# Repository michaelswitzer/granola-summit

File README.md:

# Summit by Granola Arcade

The Summit is a button box style arcade controller by Granola Arcade.

You can buy the Summit at https://granola.games

## License
The Raindrop is licensed under a <a rel="license" href="http://creativecommons.org/licenses/by-nc-sa/4.0/">Creative Commons Attribution-NonCommercial-ShareAlike 4.0 International License</a>. In simple terms, this means you are welcome to use or remix these designs to build your own controller free of cost. You are *not* permitted to sell the Summit commercially. You also can't republish the designs without attribution and without carrying this license forward into your new designs. For more information see the license file in this repository.

## How to build
To build your own Summit, import the PCB designs and bill of materials using KiCAD. I provided a list of parts that use JLCPCB's part assembly services, since that is the company I use to manufacture the PCB. You can use these files as a starting point for building your own PCB.

The .step file for the case is optimized for FDM 3D printers. I recommend PLA with at least 15% infill but you can use any material you wish. The case has designed break-away supports that you will remove after printing. It should already be aligned in the correct orientation.

The keycap files are also included, for use with Kailh Choc V2 stems (MX style). You may need to adjust the x-y hole and contour compensation values in your slicer for proper fitment.

You will need to source your own key switches. The Summit uses Kailh low-profile Choc keyboard switches.

Once you have the case, switches and keycaps, you simply slide the PCB into the top of the case and then attach the switches and keycaps to assemble. Then plug the controller into your PC and upload the firmware.

## Firmware
The Summit is designed to use the <a rel="GP2040-CE firmware" href="https://github.com/OpenStickCommunity/GP2040-CE">GP2040-CE firmware</a>.

## Credits
The Raindrop was designed by Michael Switzer. The GP2040-CE firmware is maintained by <a href="https://github.com/OpenStickCommunity">OpenStickCommunity</a>. This project was inspired by the <a href="https://github.com/jfedor2/flatbox">Flatbox</a>.

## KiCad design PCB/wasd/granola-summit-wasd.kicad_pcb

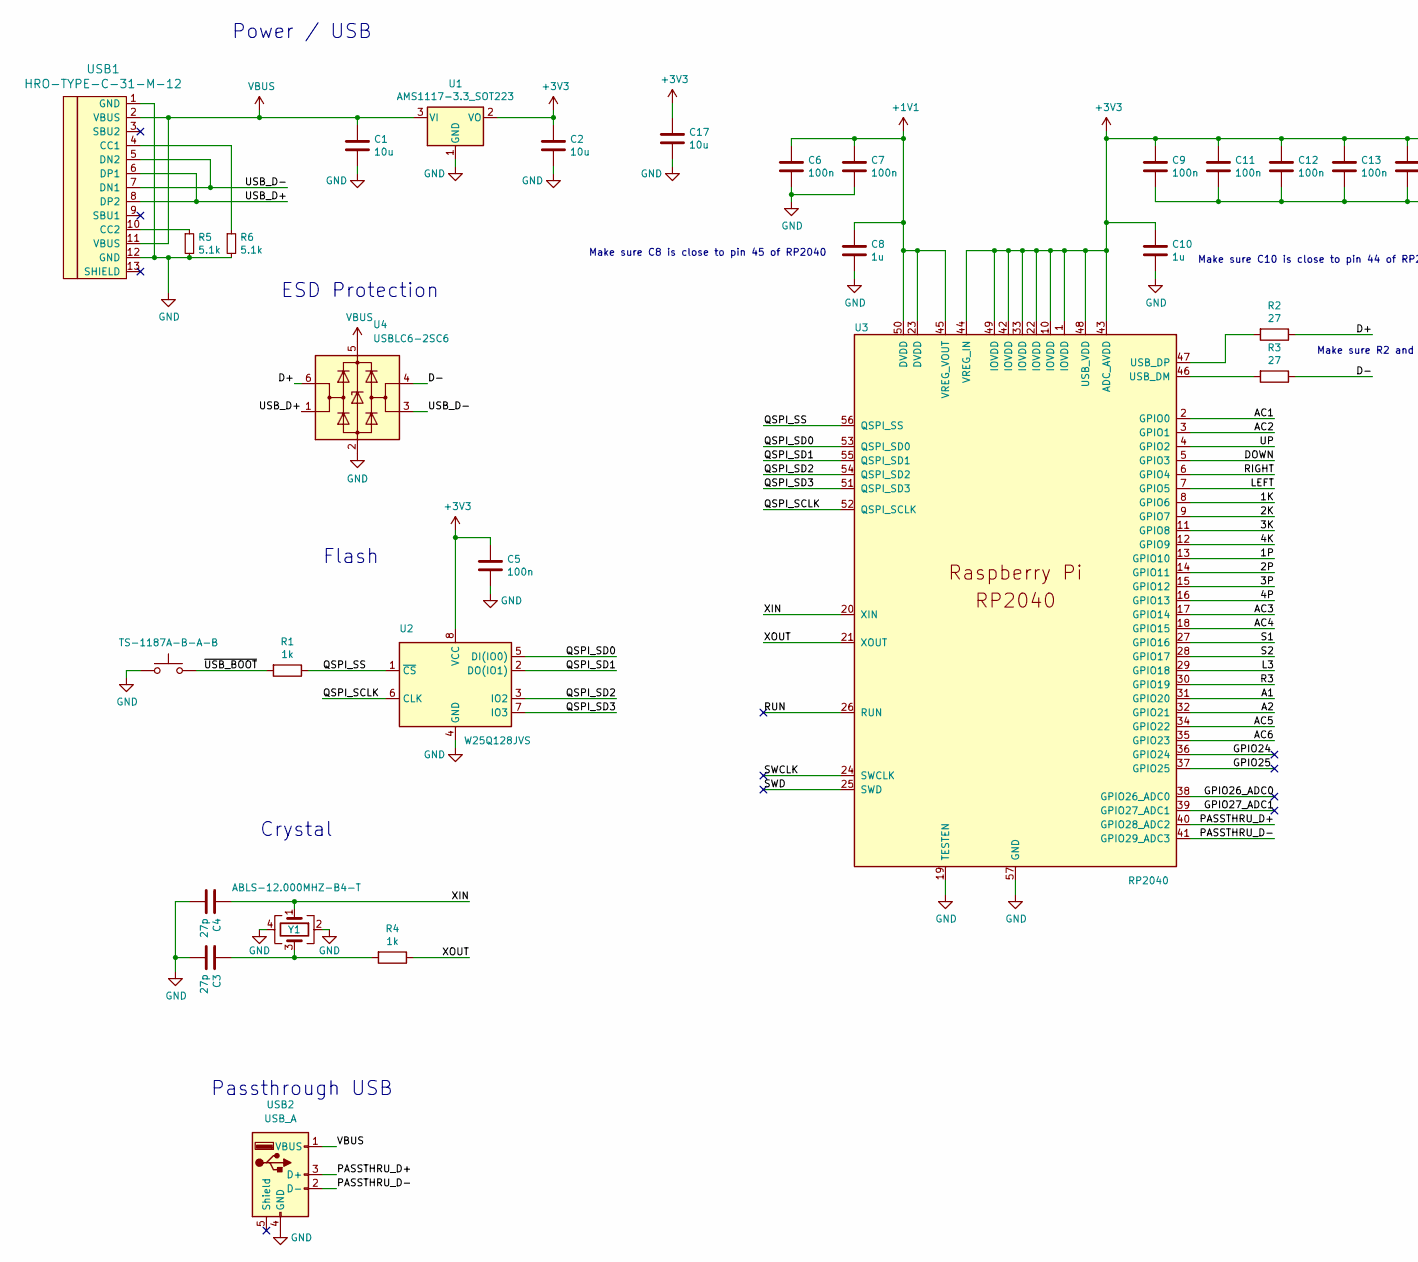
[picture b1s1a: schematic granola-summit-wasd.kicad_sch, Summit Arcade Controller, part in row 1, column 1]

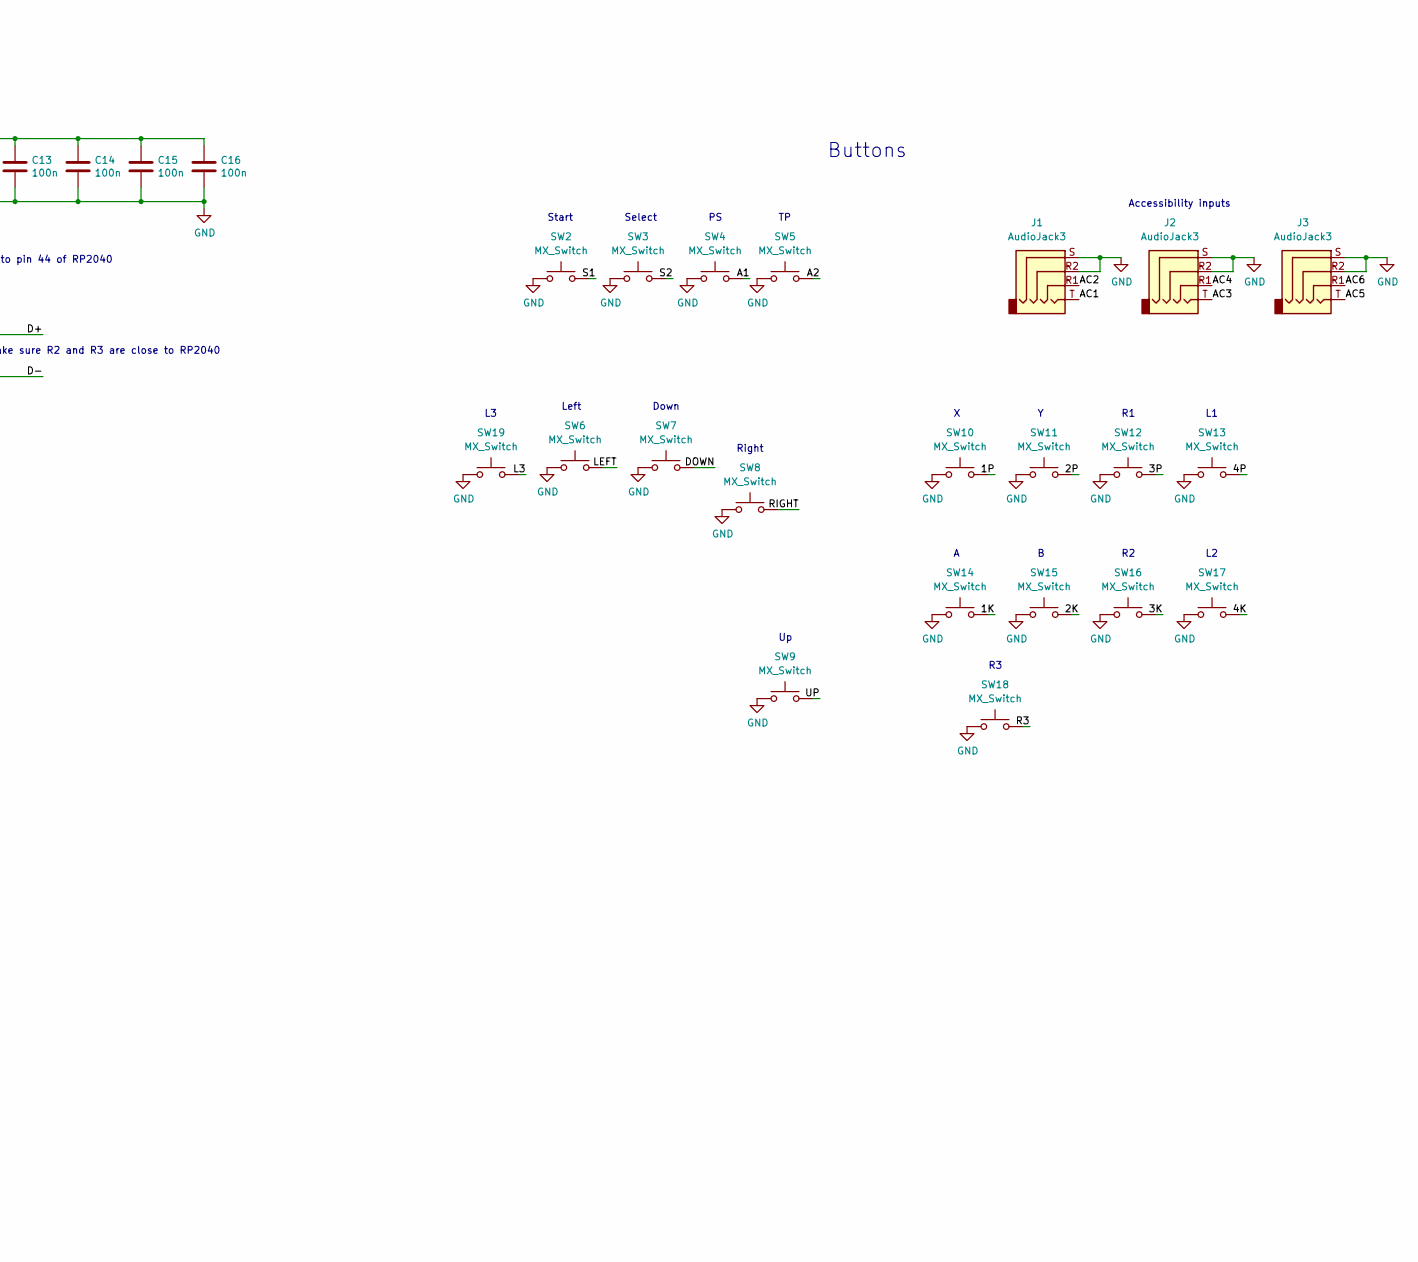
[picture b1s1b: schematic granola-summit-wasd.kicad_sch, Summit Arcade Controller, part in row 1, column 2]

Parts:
C1, C2, C17: 10u; C_0805_2012Metric; LCSC C83061
C3, C4: 27p; C_0402_1005Metric; LCSC C147436
C5, C6, C7, C9, C11, C12, C13, C14, C15, C16: 100n; C_0402_1005Metric; LCSC C115671
C8, C10: 1u; C_0402_1005Metric; LCSC C5137485
J1, J2, J3: AudioJack3; Jack_3.5mm_PJ320D_Horizontal
R1, R4: 1k; C_0402_1005Metric; LCSC C105637
R2, R3: 27; C_0402_1005Metric; LCSC C2909343
R5, R6: 5.1k; R_0402_1005Metric; LCSC C25905
SW1: TS-1187A-B-A-B; SW_Push_1P1T_XKB_TS-1187A; LCSC C318884
SW2, SW3, SW4, SW5, SW6, SW7, SW8, SW9, SW10, SW11, SW12, SW13, SW14, SW15, SW16, SW17, SW18, SW19: MX_Switch; SW_Hotswap_Kailh_Choc_V1V2_1.00u
U1: AMS1117-3.3_SOT223; SOT-223-3_TabPin2; LCSC C5250992
U2: W25Q128JVS; SOIC-8_5.23x5.23mm_P1.27mm; LCSC C97521
U3: RP2040; RP2040-QFN-56; LCSC C2040
U4: USBLC6-2SC6; SOT-23-6
USB1: HRO-TYPE-C-31-M-12; HRO-TYPE-C-31-M-12-Assembly; LCSC C165948
USB2: USB_A; USB-A-SMD_C42591; LCSC C42591
Y1: ABLS-12.000MHZ-B4-T; Crystal_SMD_3225-4Pin_3.2x2.5mm; LCSC C9002

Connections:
+1V1: C6.1, C7.1, C8.1, U3.23 (DVDD), U3.45 (VREG_VOUT), U3.50 (DVDD)
+3V3: C2.1, C5.1, C9.1, C10.1, C11.1, C12.1, C13.1, C14.1, C15.1, C16.1, C17.1, U1.2 (VO), U2.8 (VCC), U3.1 (IOVDD), U3.10 (IOVDD), U3.22 (IOVDD), U3.33 (IOVDD), U3.42 (IOVDD), U3.43 (ADC_AVDD), U3.44 (VREG_IN), U3.48 (USB_VDD), U3.49 (IOVDD)
/1K: SW14.1 (A), U3.8 (GPIO6)
/1P: SW10.1 (A), U3.13 (GPIO10)
/2K: SW15.1 (A), U3.9 (GPIO7)
/2P: SW11.1 (A), U3.14 (GPIO11)
/3K: SW16.1 (A), U3.11 (GPIO8)
/3P: SW12.1 (A), U3.15 (GPIO12)
/4K: SW17.1 (A), U3.12 (GPIO9)
/4P: SW13.1 (A), U3.16 (GPIO13)
/A1: SW4.1 (A), U3.31 (GPIO20)
/A2: SW5.1 (A), U3.32 (GPIO21)
/AC1: J1.T, U3.2 (GPIO0)
/AC2: J1.R1, U3.3 (GPIO1)
/AC3: J2.T, U3.17 (GPIO14)
/AC4: J2.R1, U3.18 (GPIO15)
/AC5: J3.T, U3.34 (GPIO22)
/AC6: J3.R1, U3.35 (GPIO23)
/D+: R2.1, U4.6 (I/O1)
/D-: R3.1, U4.4 (I/O2)
/DOWN: SW7.1 (A), U3.5 (GPIO3)
/GPIO24: U3.36 (GPIO24)
/GPIO25: U3.37 (GPIO25)
/GPIO26_ADC0: U3.38 (GPIO26_ADC0)
/GPIO27_ADC1: U3.39 (GPIO27_ADC1)
/L3: SW19.1 (A), U3.29 (GPIO18)
/LEFT: SW6.1 (A), U3.7 (GPIO5)
/PASSTHRU_D+: U3.40 (GPIO28_ADC2), USB2.3 (D+)
/PASSTHRU_D-: U3.41 (GPIO29_ADC3), USB2.2 (D-)
/QSPI_SCLK: U2.6 (CLK), U3.52 (QSPI_SCLK)
/QSPI_SD0: U2.5 (DI(IO0)), U3.53 (QSPI_SD0)
/QSPI_SD1: U2.2 (DO(IO1)), U3.55 (QSPI_SD1)
/QSPI_SD2: U2.3 (IO2), U3.54 (QSPI_SD2)
/QSPI_SD3: U2.7 (IO3), U3.51 (QSPI_SD3)
/QSPI_SS: R1.1, U2.1 (~CS), U3.56 (QSPI_SS)
/R3: SW18.1 (A), U3.30 (GPIO19)
/RIGHT: SW8.1 (A), U3.6 (GPIO4)
/RUN: U3.26 (RUN)
/S1: SW2.1 (A), U3.27 (GPIO16)
/S2: SW3.1 (A), U3.28 (GPIO17)
/SWCLK: U3.24 (SWCLK)
/SWD: U3.25 (SWD)
/UP: SW9.1 (A), U3.4 (GPIO2)
/USB_D+: U4.1 (I/O1), USB1.6 (DP1), USB1.8 (DP2)
/USB_D-: U4.3 (I/O2), USB1.5 (DN2), USB1.7 (DN1)
/XIN: C4.1, U3.20 (XIN), Y1.1
/XOUT: R4.1, U3.21 (XOUT)
/~USB_BOOT: R1.2, SW1.1
GND: C1.2, C2.2, C3.2, C4.2, C5.2, C6.2, C7.2, C8.2, C9.2, C10.2, C11.2, C12.2, C13.2, C14.2, C15.2, C16.2, C17.2, J1.R2, J1.S, J2.R2, J2.S, J3.R2, J3.S, R5.2, R6.2, SW1.2, SW2.2 (B), SW3.2 (B), SW4.2 (B), SW5.2 (B), SW6.2 (B), SW7.2 (B), SW8.2 (B), SW9.2 (B), SW10.2 (B), SW11.2 (B), SW12.2 (B), SW13.2 (B), SW14.2 (B), SW15.2 (B), SW16.2 (B), SW17.2 (B), SW18.2 (B), SW19.2 (B), U1.1 (GND), U2.4 (GND), U3.19 (TESTEN), U3.57 (GND), U4.2 (GND), USB1.1 (GND), USB1.12 (GND), USB2.4 (GND), Y1.2, Y1.4
unnamed: C3.1, R4.2, Y1.3
unnamed: R3.2, U3.46 (USB_DM)
unnamed: R2.2, U3.47 (USB_DP)
unnamed: R6.1, USB1.4 (CC1)
unnamed: R5.1, USB1.10 (CC2)
VBUS: C1.1, U1.3 (VI), U4.5 (VBUS), USB1.2 (VBUS), USB1.11 (VBUS), USB2.1 (VBUS)

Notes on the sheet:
ESD Protection
Right
Start
Down
Left
Make sure R2 and R3 are close to RP2040
Crystal
Passthrough USB
Make sure C10 is close to pin 44 of RP2040
Flash
Accessibility inputs
Power / USB
Select
Buttons
Make sure C8 is close to pin 45 of RP2040

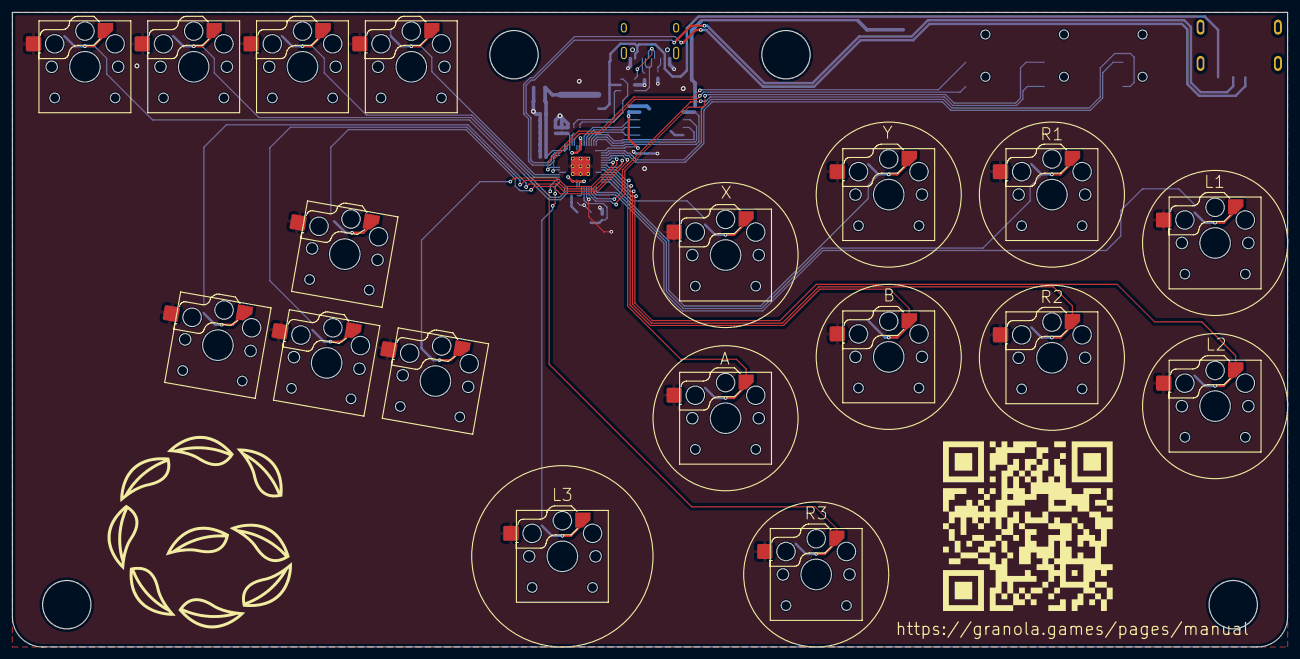
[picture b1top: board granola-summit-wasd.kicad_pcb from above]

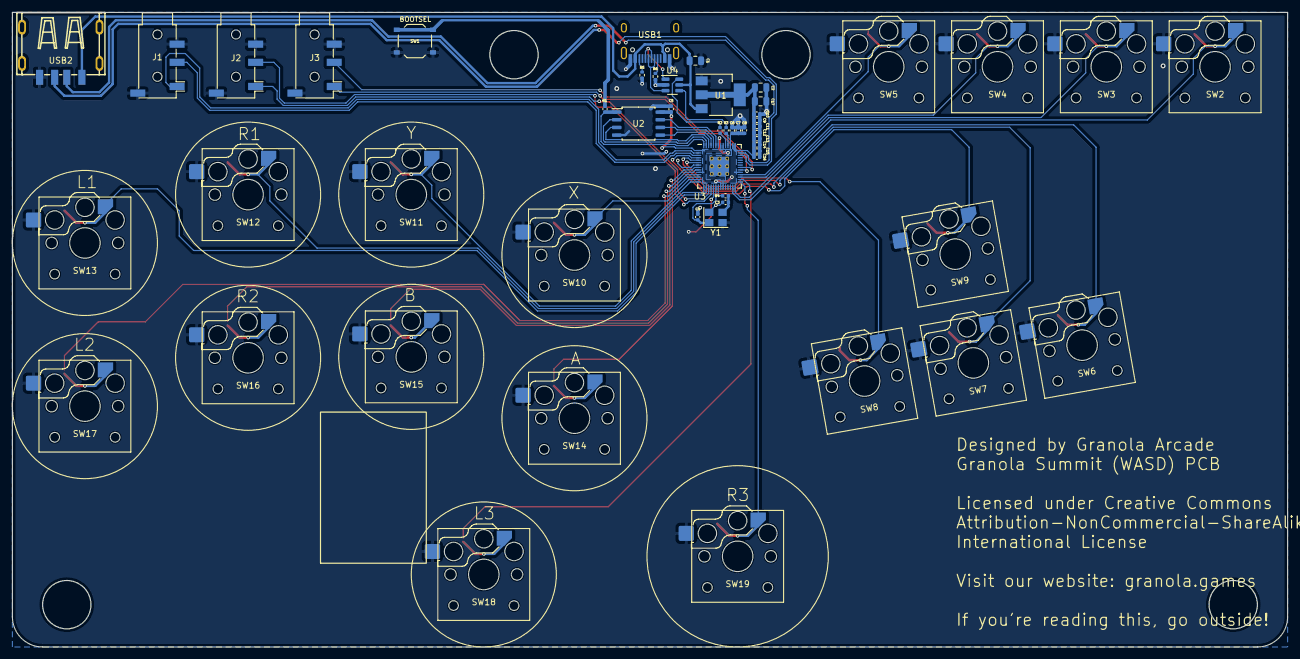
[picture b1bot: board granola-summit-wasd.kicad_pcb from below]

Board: 2 copper layers, 210.9 x 104.9 mm, 52 parts (52 on the bottom side), 48 nets.

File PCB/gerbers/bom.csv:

Comment,Designator,Footprint,LCSC Part Number
10uF,"C1,C2",Capacitor_SMD:C_0805_2012Metric,C83061
27p,"C3,C4",Capacitor_SMD:C_0402_1005Metric,C147436
100nF,"C5,C6,C7,C9,C11,C12,C13,C14,C15,C16",Capacitor_SMD:C_0402_1005Metric,C115671
1uF,"C8,C10",Capacitor_SMD:C_0402_1005Metric,C5137485
10uF,C17,Capacitor_SMD:C_0805_2012Metric,C83061
"HRO-TYPE-C-31-M-12","USB1","Type-C:HRO-TYPE-C-31-M-12-Assembly","C165948"
"USB_A","USB2","USB-A-SMD_C42591","C42591"
1k,"R1,R5",Capacitor_SMD:C_0402_1005Metric,C105637
"5.1k","R6,R7","Resistor_SMD:R_0402_1005Metric","C25905"
27 ohm,"R3,R4,R8,R9",Capacitor_SMD:C_0402_1005Metric,C2909343
MX_Switch,"SW1,SW2,SW3,SW4,SW5,SW6,SW7,SW8,SW9,SW10,SW11,SW12,SW13,SW14,SW15,SW16,SW17,SW18","Kailh:SW_Hotswap_Kailh_Choc_V1V2_1.00u_reversible,Kailh:SW_Hotswap_Kailh_Choc_V1V2_1.00u_24mm_reversible,Kailh:SW_Hotswap_Kailh_Choc_V1V2_1.00u_30mm_reversible",C5333465
AMS1117,U1,Package_TO_SOT_SMD:SOT-223-3_TabPin2,C5250992
W25Q128JVS,U2,Package_SO:SOIC-8_5.23x5.23mm_P1.27mm,C97521
RP2040,U3,RP2040_minimal:RP2040-QFN-56,C2040
Crystal_GND24,Y1,Crystal:Crystal_SMD_3225-4Pin_3.2x2.5mm,C9002
AudioJack3,"J1,J2,J3",Connector_Audio:Jack_3.5mm_PJ320D_Horizontal,C431535

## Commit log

2024-06-08 Added southpaw and big summit cases. +1mm thickness to original case.
2024-10-03 v2.0 board design, WASD model

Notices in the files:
PCB/wasd/granola-summit-wasd.kicad_pcb:
Licensed under Creative Commons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
